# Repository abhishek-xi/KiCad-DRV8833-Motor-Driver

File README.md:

# KiCad DRV8833 Motor Driver

A custom dual H-Bridge motor driver PCB based on the Texas Instruments DRV8833 motor driver IC. Designed in KiCad for robotics, embedded systems, and small DC motor control applications.

## Features

- Dual DC motor control
- DRV8833 dual H-Bridge motor driver
- Sleep mode support
- Fault monitoring output
- Onboard power indicator LED
- Power supply decoupling capacitors
- Compact PCB design
- Easy connector-based interfacing

## Hardware Specifications

| Parameter | Value |
|------------|---------|
| Motor Driver IC | DRV8833 |
| Motor Channels | 2 |
| Motor Supply Voltage | 2.7V – 10.8V |
| Logic Interface | 3.3V / 5V Compatible |
| Control Inputs | AIN1, AIN2, BIN1, BIN2 |
| Fault Output | FAULT |
| Sleep Control | SLEEP |

## Schematic

The design includes:

- DRV8833 motor driver IC
- Power filtering capacitors
- Status LED
- Motor output connectors
- Control signal connectors
- Fault monitoring output

## Pinout

### Control Header

| Pin | Signal |
|------|---------|
| 1 | AIN1 |
| 2 | AIN2 |
| 3 | VCC |
| 4 | GND |
| 5 | BIN1 |
| 6 | BIN2 |

### Motor Header

| Pin | Signal |
|------|---------|
| 1 | SLEEP |
| 2 | AOUT1 |
| 3 | AOUT2 |
| 4 | BOUT1 |
| 5 | BOUT2 |
| 6 | FAULT |

## Applications

- Mobile robots
- Line follower robots
- Autonomous vehicles
- Embedded motor control systems
- Educational robotics projects
- Small DC motor applications

## Design Tools

- KiCad 9
- DRV8833 Datasheet

## Future Improvements

- Current sensing support
- Reverse polarity protection
- Screw terminal connectors
- Test points for debugging

## License

This project is released under the MIT License.

## Author

Abhishek B Kumbar  
ECE Student | PCB Design | Embedded Systems

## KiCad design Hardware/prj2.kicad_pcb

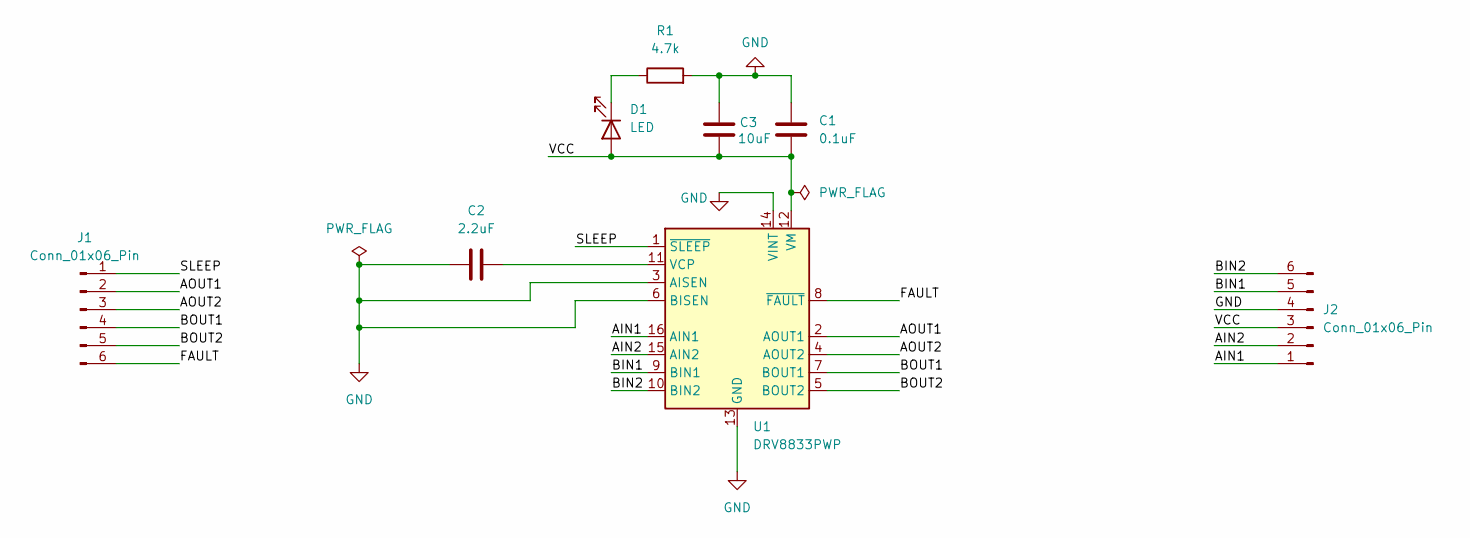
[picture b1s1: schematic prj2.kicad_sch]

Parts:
C1: 0.1uF; C_0402_1005Metric
C2: 2.2uF; C_0402_1005Metric
C3: 10uF; C_0402_1005Metric
D1: LED; D_SOD-123
J1, J2: Conn_01x06_Pin; PinHeader_1x06_P2.54mm_Vertical
R1: 4.7k; R_0603_1608Metric
U1: DRV8833PWP; HTSSOP-16-1EP_4.4x5mm_P0.65mm_EP3.4x5mm_Mask2.46x2.31mm_The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

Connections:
/AIN1: J2.1, U1.16 (AIN1)
/AIN2: J2.2, U1.15 (AIN2)
/AOUT1: J1.2, U1.2 (AOUT1)
/AOUT2: J1.3, U1.4 (AOUT2)
/BIN1: J2.5, U1.9 (BIN1)
/BIN2: J2.6, U1.10 (BIN2)
/BOUT1: J1.4, U1.7 (BOUT1)
/BOUT2: J1.5, U1.5 (BOUT2)
/FAULT: J1.6, U1.8 (~FAULT)
/SLEEP: J1.1, U1.1 (~SLEEP)
/VCC: C1.2, C3.2, D1.2 (A), J2.3, U1.12 (VM)
GND: C1.1, C2.1, C3.1, J2.4, R1.2, U1.3 (AISEN), U1.6 (BISEN), U1.13 (GND), U1.14 (VINT), U1.17 (GND)
unnamed: D1.1 (K), R1.1
unnamed: C2.2, U1.11 (VCP)

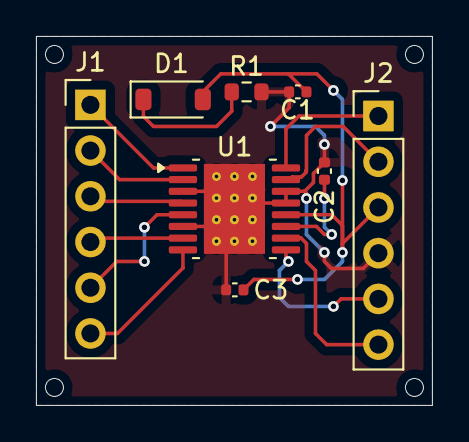
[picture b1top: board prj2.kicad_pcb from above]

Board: 2 copper layers, 22.0 x 20.5 mm, 8 parts (0 on the bottom side), 14 nets.
